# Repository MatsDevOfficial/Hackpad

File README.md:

# Mats's hackpad
Hello! This is my first ever hardware project, so i hope you like it..

## PCB
Here are pictures of my pcb:

| **Schematic** | **PCB** |
|---------------|---------|
|||

[x] I ran DRC and there are 0 errors

## CAD
Designed using AutoDask Fusion! 

(Only the top)

Everything fits together with 4 m3 screws and bolts. * The original design did not include a top, but i added it after it was requested. ** Enlargened to top for the oled

## Firmware

I wrote the firmware using kmk, you can see it inside the repo. 

Still have to add the OLED firmware, but have exams next week and wont otherwise have enough time to change any hardware requirements.

## Notes
Making the pad was fun!The original design did not include a top, but i added it after it was requested.

## BOM
[BOM](/Macropad.csv)

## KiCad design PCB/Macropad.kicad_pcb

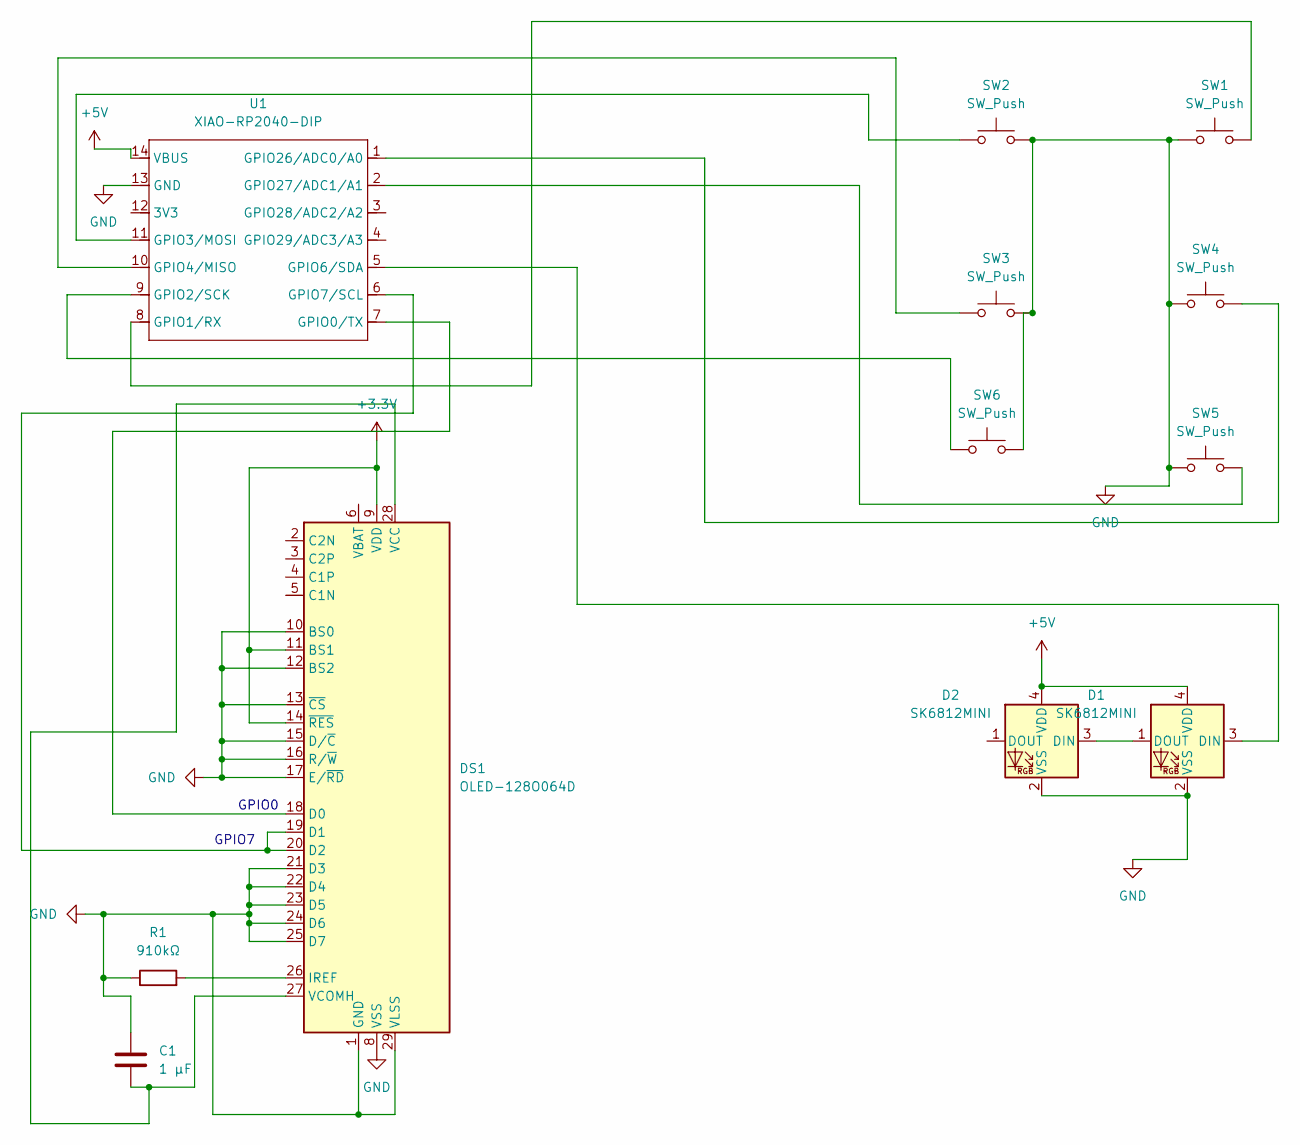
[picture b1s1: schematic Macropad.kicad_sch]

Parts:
C1: 1 µF; C_0402_1005Metric
D1, D2: SK6812MINI; LED_SK6812MINI_PLCC4_3.5x3.5mm_P1.75mm
DS1: OLED-128O064D
R1: 910kΩ; R_Axial_DIN0204_L3.6mm_D1.6mm_P1.90mm_Vertical
SW1, SW2, SW3, SW4, SW5, SW6: SW_Push; SW_Cherry_MX_1.00u_PCB
U1: XIAO-RP2040-DIP; Seeeduino XIAO-MOUDLE14P-2.54-21X17.8MM

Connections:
+3.3V: DS1.9 (VDD), DS1.11 (BS1), DS1.14 (~RES)
+5V: D1.4 (VDD), D2.4 (VDD), U1.14 (VBUS)
GND: C1.1, D1.2 (VSS), D2.2 (VSS), DS1.1 (GND), DS1.8 (VSS), DS1.10 (BS0), DS1.12 (BS2), DS1.13 (~CS), DS1.15 (D/~C), DS1.16 (R/~W), DS1.17 (E/~RD), DS1.21 (D3), DS1.22 (D4), DS1.23 (D5), DS1.24 (D6), DS1.25 (D7), DS1.29 (VLSS), DS1.30 (GND), R1.1, SW1.2, SW2.1, SW3.1, SW4.2, SW5.2, SW6.1, U1.13 (GND)
unnamed: D1.3 (DIN), U1.5 (GPIO6/SDA)
unnamed: D1.1 (DOUT), D2.3 (DIN)
unnamed: DS1.18 (D0), U1.7 (GPIO0/TX)
unnamed: DS1.19 (D1), DS1.20 (D2), U1.6 (GPIO7/SCL)
unnamed: DS1.26 (IREF), R1.2
unnamed: C1.2, DS1.27 (VCOMH), DS1.28 (VCC)
unnamed: SW1.1, U1.8 (GPIO1/RX)
unnamed: SW6.2, U1.9 (GPIO2/SCK)
unnamed: SW2.2, U1.11 (GPIO3/MOSI)
unnamed: SW3.2, U1.10 (GPIO4/MISO)
unnamed: SW4.1, U1.1 (GPIO26/ADC0/A0)
unnamed: SW5.1, U1.2 (GPIO27/ADC1/A1)

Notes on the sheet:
GPIO0
GPIO7

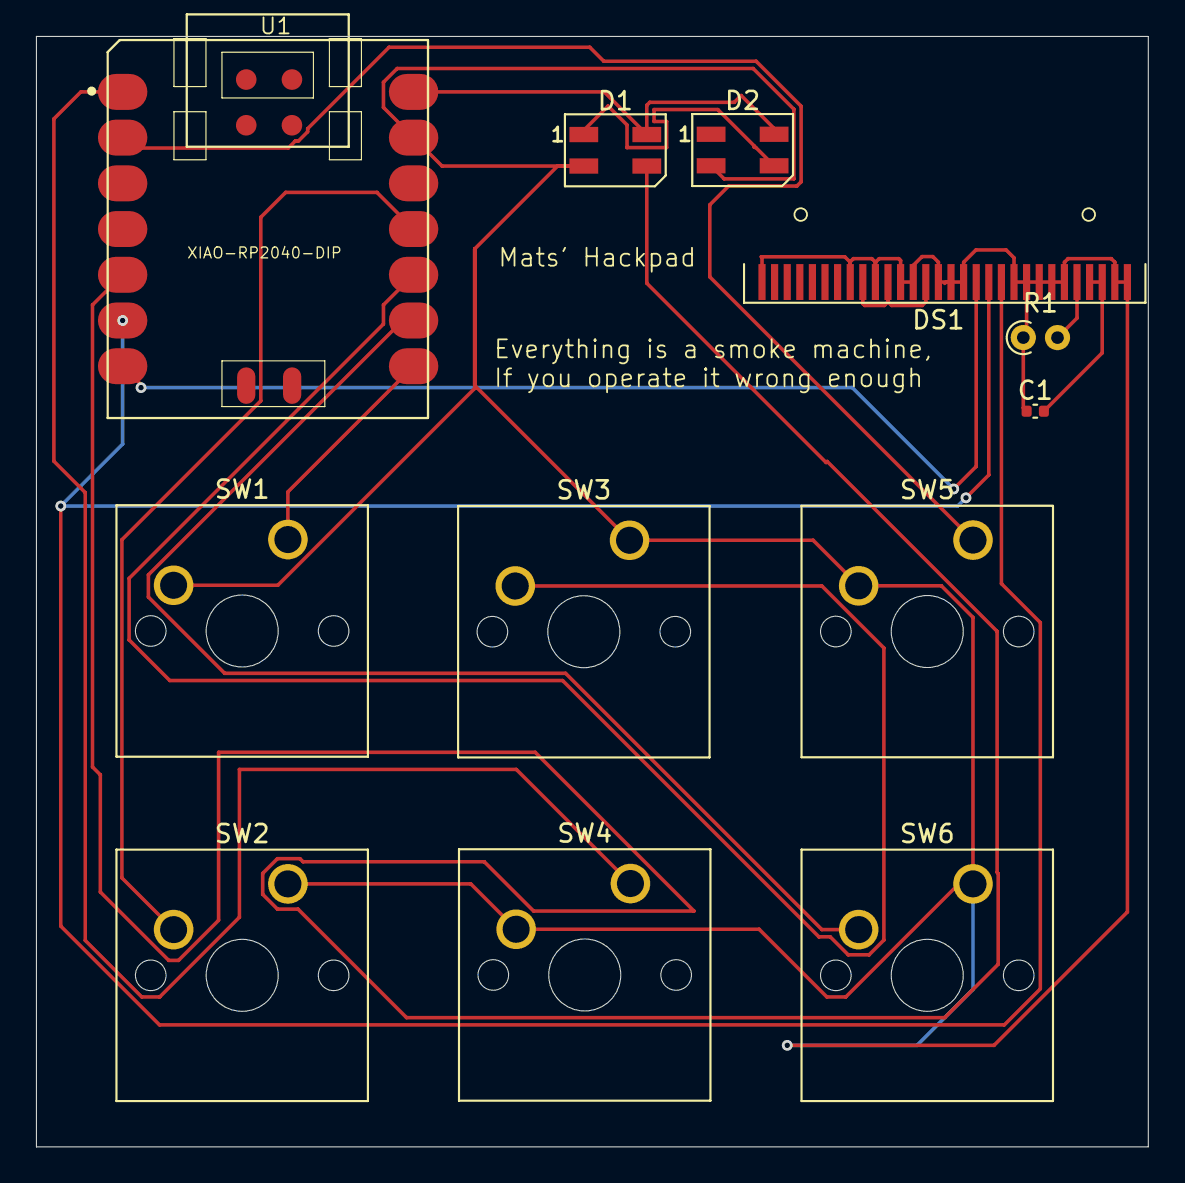
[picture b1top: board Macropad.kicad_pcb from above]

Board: 2 copper layers, 61.8 x 61.7 mm, 12 parts (0 on the bottom side), 15 nets.

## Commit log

2025-11-28 Hackpad Mats
2025-11-28 Fix README
2025-12-01 Add a top
2026-01-15 OLED
